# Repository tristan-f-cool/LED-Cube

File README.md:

# 3×3×3 Blue LED Cube

A 27-LED cube built around a custom ATmega328P controller PCB, programmed using the Arduino Uno platform. This project brings together the PCB design, Arduino firmware, and a 3D-printable base platform stand.

The animations are written as individual C++ functions, with reusable helpers for LEDs, layers, columns, and faces.

**[Watch the cube on YouTube](https://youtu.be/wXxeV7et9vc?si=_cEj829iDm0wTGiT)**

## Project at a glance

| Feature | Details |
| --- | --- |
| Display | 3 layers × 9 columns: 27 blue LEDs |
| Controller | ATmega328P on a custom PCB |
| Firmware | Arduino sketch with 16 effect functions |
| Playback | Sequential, random, or development mode |
| Hardware design | EAGLE schematic, board layout, and exported parts list |
| Mechanical design | STL files for the base and a separate LED grid |

## Hardware

The controller uses nine column outputs and three transistor-switched layer outputs. The firmware uses Arduino pin names, so the same mapping is easy to follow when working with an Uno-compatible ATmega328P setup.

| Connection | Arduino pins | Circuit |
| --- | --- | --- |
| Columns 1–9 | D2–D10, respectively | 220 Ω series resistors |
| Layers 1–3 | A0–A2, respectively | 2N3904 NPN layer drivers |
| Serial diagnostics | Serial at 9600 baud | Effect and playback-mode messages |

The schematic includes a 16 MHz crystal, reset circuit, 7805 regulator, serial programming header, and ICSP header. See the design files and parts list for the full circuit.

<details>
<summary>Schematic</summary>

</details>

| PCB layout | PCB 3D view |
| --- | --- |
|  |  |

- [EAGLE schematic](PCB/LEDCube-3x3x3/LEDCube-3x3x3.sch)
- [EAGLE board](PCB/LEDCube-3x3x3/LEDCube-3x3x3.brd)
- [Exported parts list](PCB/LEDCube-3x3x3/LEDCube-3x3x3-PCBA_BOM.txt)
- [Archived PCB design package](PCB/LEDCube-3x3x3/LEDCube-3x3x3_2026-02-08.zip)

## Firmware

The complete sketch is in [`code/LEDCube-3x3x3/LEDCube-3x3x3.ino`](code/LEDCube-3x3x3/LEDCube-3x3x3.ino). It uses Arduino core functions and has no external library includes.

### Program flow

```mermaid
flowchart TD
    A[Power on or reset] --> B["setup(): start Serial, seed random generator, configure pins"]
    B --> C["loop(): read playback setting"]
    C --> D{Mode}
    D -->|DEV| E[Select effect 0]
    D -->|SEQUENCE| F[Advance effect index; wrap after 15]
    D -->|RANDOM| G[Choose effect index from 0 to 15]
    E --> H["LEDCube(): log index and dispatch effect"]
    F --> H
    G --> H
    H --> I["Effect0() through Effect15()"]
    I --> J[LED, layer, column, and face helpers]
    J --> K["digitalWrite() and delay()"]
    K --> L[Clear LEDs and pause 500 ms]
    L --> C
```

Effects directly set the layer and column outputs and use blocking delays for timing. There is no separate background display-refresh task in this sketch.

### Playback modes

Change the setting near the top of the sketch before uploading:

```cpp
mode setting = SEQUENCE;
```

| Mode | Behavior |
| --- | --- |
| `DEV` | Repeats `Effect0()` for development and testing |
| `SEQUENCE` | Advances through effect indices, wrapping from 15 to 0 |
| `RANDOM` | Selects an effect index with `random(16)` |

In the current sketch, `effect_index` starts at 0 and is incremented before dispatch in `SEQUENCE` mode, so the first effect after reset is `Effect1()`.

### Included effects

| Function | Animation |
| --- | --- |
| `Effect0()` | Full-cube flashing with decreasing delay |
| `Effect1()` | Random LED flashes |
| `Effect2()` | Alternating corners and center |
| `Effect3()` | Full-column spirals |
| `Effect4()` | Random columns moving up and down |
| `Effect5()` | Layer spirals, inward and outward |
| `Effect6()` | Traveling faces along the three axes |
| `Effect7()` | Alternating X and cross patterns |
| `Effect8()` | Corners and diamonds |
| `Effect9()` | Spinning faces through the center |
| `Effect10()` | Rotating perimeter faces |
| `Effect11()` | Perimeter column chase |
| `Effect12()` | Perimeter wave |
| `Effect13()` | Figure-eight paths |
| `Effect14()` | Zigzag paths |
| `Effect15()` | Three-dimensional X paths |

### Writing an effect

The helper API uses **layer numbers 1–3** and **column numbers 1–9**. For example:

```cpp
void MyEffect()
{
  LED_ALL_OFF();
  LED_ON(1, 5);       // Center LED of the bottom layer
  delay(200);
  LED_ALL_OFF();
  LAYER_SQUARE(3);   // Perimeter of the top layer
  delay(200);
  LED_ALL_OFF();
}
```

To add an effect, give it a case in `LEDCube()` and update both the sequential wrap limit and random-selection range. Outputs remain set until another helper changes them; clear the previous pattern when needed.

Column numbering follows the sketch's wiring diagram, repeated on each layer:

```text
1   4   7
2   5   8
3   6   9
```

Layer 1 is the bottom, layer 2 is the middle, and layer 3 is the top.

### Current source notes

The checked-in firmware has a few items to review before extending it:

- `LED_ALL_ON()` and `LED_ALL_OFF()` iterate through layer 4 and column 10, beyond the arrays. Their valid limits are 3 layers and 9 columns.
- `LED_RANDOM_ON()` and `LED_RANDOM_OFF()` can generate zero, although the helper API is one-based. `Effect4()` also uses `random(10)` for a column and can select zero. Valid selections use `random(1, 4)` for layers and `random(1, 10)` for columns.
- The dispatch case for effect 10 has no `break`, so selecting effect 10 also runs effect 11.
- The firmware comment describes 2.2 kΩ transistor base resistors, while the schematic and exported parts list specify 22 kΩ. Confirm the fitted values against your board revision.

These notes describe the source as supplied; they are not firmware changes.

## Loading the sketch

1. Open `code/LEDCube-3x3x3/LEDCube-3x3x3.ino` in the Arduino IDE.
2. Select the Arduino Uno target for an ATmega328P configured with the Uno bootloader and 16 MHz clock.
3. Choose the desired playback mode in the sketch.
4. Upload using your board's programming connection. A chip without a bootloader needs an ISP programmer to provision it or program the firmware directly.
5. Open Serial Monitor at **9600 baud** to see the mode and effect index.

## Printed base and CAD

The printed base supports the controller PCB and gives the cube a finished platform.

- [Base platform STL](CAD/base.stl)
- [LED grid STL](CAD/ledgrid4x4.stl) — a separate 4×4 grid model included in the repository; the electronic cube documented here is 3×3×3.

<details>
<summary>LED grid render</summary>

</details>

<!-- Add your preferred material, layer height, infill, support settings, and mounting hardware here. -->

## Repository guide

```text
.
├── CAD/                         Base and LED grid STL files
├── code/LEDCube-3x3x3/          Arduino firmware
├── PCB/LEDCube-3x3x3/           EAGLE files, parts list, and archive
├── media/                       Photos, design renders, and demo videos
├── .gitattributes               Git LFS tracking rules
└── README.md
```

### Photos and video

Watch the [YouTube demonstration](https://youtu.be/wXxeV7et9vc?si=_cEj829iDm0wTGiT), or download the original clips: [demo](media/demo.mp4), [dark-room demo](media/demo-dark.mp4), and [demo 2](media/demo2.mp4).

### Getting the media and CAD files

The binary assets use Git LFS. With Git LFS installed, clone the repository and retrieve its assets:

```sh
git lfs install
git clone https://github.com/tristan-f-cool/LED-Cube.git
cd LED-Cube
git lfs pull
```

If an image or STL opens as a short text file beginning with `version https://git-lfs.github.com/spec/v1`, it is an LFS pointer; run `git lfs pull` to retrieve the actual asset.

## Author

Designed and built by **Tristan Cool**.

<!-- Add a LICENSE file and a license section when you have chosen terms for the hardware, firmware, and CAD. -->

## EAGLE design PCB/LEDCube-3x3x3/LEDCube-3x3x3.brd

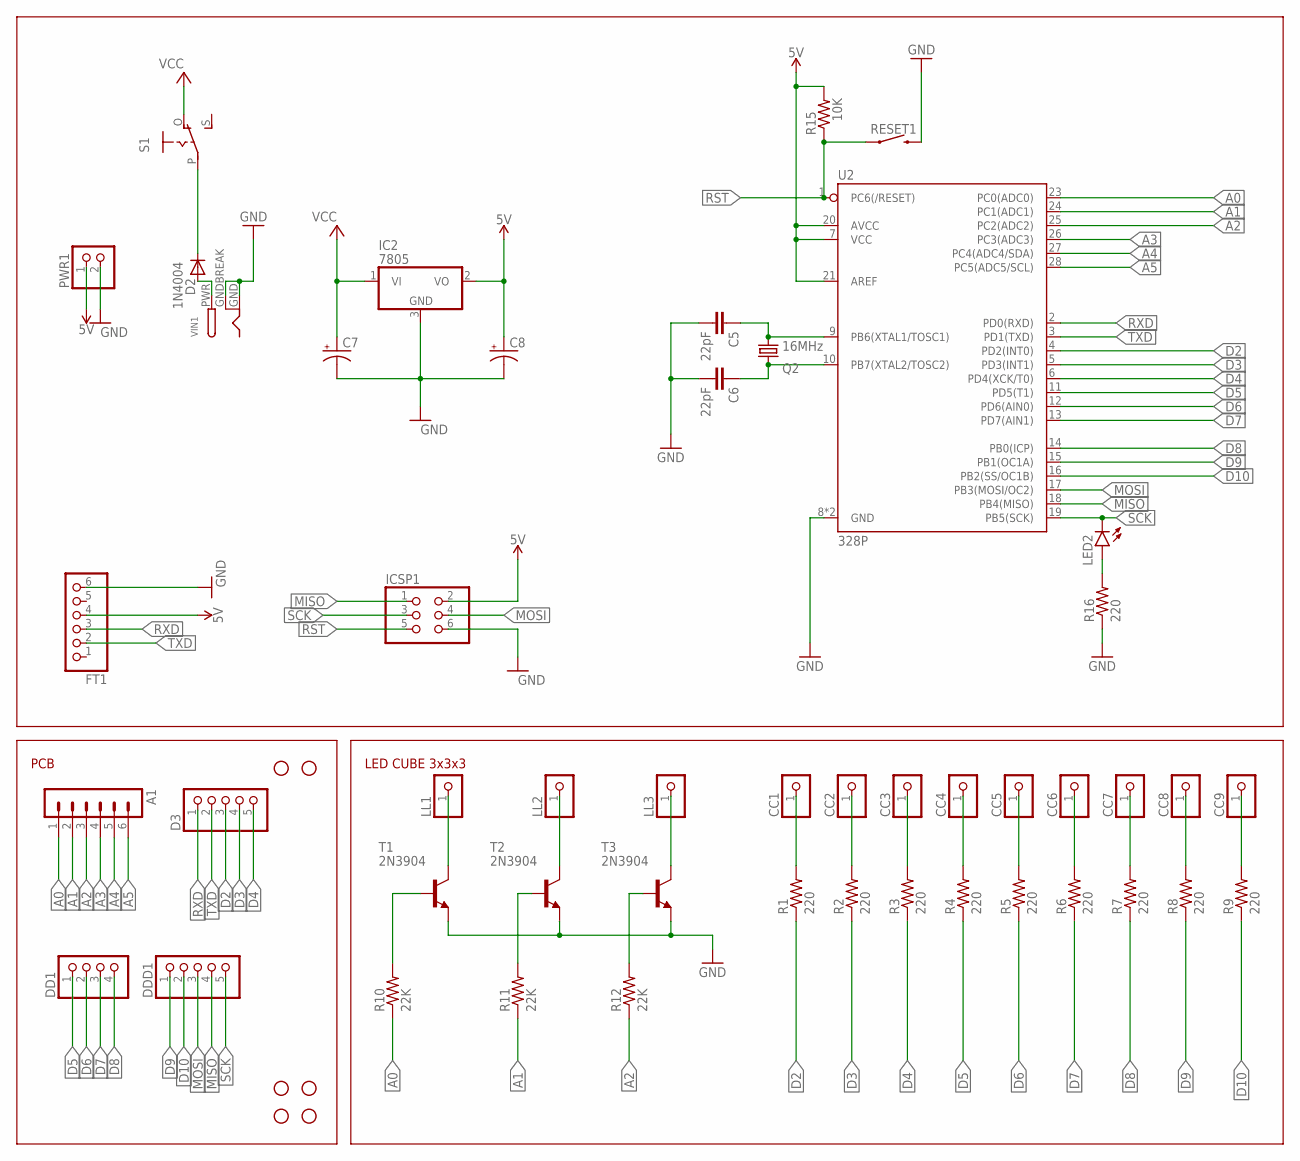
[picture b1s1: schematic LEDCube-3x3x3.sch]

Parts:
A1: MA06-1
C5, C6: 22pF; CAP-PTH-2.54
C7, C8: CPOL-USE1.8-4; E1,8-4
CC1, CC2, CC3, CC4, CC5, CC6, CC7, CC8, CC9: PINHD-1X1; 1X01
D2: 1N4004; DO41-10
D3: PINHD-1X5; 1X05
DD1: PINHD-1X4; 1X04
DDD1: PINHD-1X5; 1X05
FT1: PINHD-1X6; 1X06
H1, H2, H3, H4, H7, H8: STAND-OFFTIGHT; STAND-OFF-TIGHT
IC2: 7805; TO252
ICSP1: PINHD-2X3; 2X03
LED2: LEDCHIP-LED0805; CHIP-LED0805
LL1, LL2, LL3: PINHD-1X1; 1X01
PWR1: PINHD-1X2; 1X02
Q2: 16MHz; HC49/S
R1, R2, R3, R4, R5, R6, R7, R8, R9, R16: 220; R0805
R10, R11, R12: 22K; R0805
R15: 10K; R0805
RESET1: MOMENTARY-SWITCH-SPST-PTH-6.0MM; TACTILE_SWITCH_PTH_6.0MM
S1: EG1218S; EG1218
T1, T2, T3: 2N3904; TO92
U2: 328P; DIP28
VIN1: DCBARRELPTH; DCJACK_2MM_PTH

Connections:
5V: C8.+, FT1.4, IC2.2 (VO), ICSP1.2, PWR1.1, R15.2, U2.7 (VCC), U2.20 (AVCC), U2.21 (AREF)
A0: A1.1, R10.1, U2.23 (PC0(ADC0))
A1: A1.2, R11.1, U2.24 (PC1(ADC1))
A2: A1.3, R12.1, U2.25 (PC2(ADC2))
A3: A1.4, U2.26 (PC3(ADC3))
A4: A1.5, U2.27 (PC4(ADC4/SDA))
A5: A1.6, U2.28 (PC5(ADC5/SCL))
C3: CC3.1, R3.2
D2: D3.3, R1.1, U2.4 (PD2(INT0))
D3: D3.4, R2.1, U2.5 (PD3(INT1))
D4: D3.5, R3.1, U2.6 (PD4(XCK/T0))
D5: DD1.1, R4.1, U2.11 (PD5(T1))
D6: DD1.2, R5.1, U2.12 (PD6(AIN0))
D7: DD1.3, R6.1, U2.13 (PD7(AIN1))
D8: DD1.4, R7.1, U2.14 (PB0(ICP))
D9: DDD1.1, R8.1, U2.15 (PB1(OC1A))
D10: DDD1.2, R9.1, U2.16 (PB2(SS/OC1B))
GND: C5.2, C6.2, C7.-, C8.-, FT1.6, IC2.3 (GND), ICSP1.6, PWR1.2, R16.1, RESET1.3 (2), T1.3 (E), T2.3 (E), T3.3 (E), U2.8 (GND), U2.22 (GND), VIN1.GND, VIN1.GNDBREAK
MISO: DDD1.4, ICSP1.1, U2.18 (PB4(MISO))
MOSI: DDD1.3, ICSP1.4, U2.17 (PB3(MOSI/OC2))
unnamed: R10.2, T1.2 (B)
unnamed: R11.2, T2.2 (B)
unnamed: R12.2, T3.2 (B)
unnamed: LL1.1, T1.1 (C)
unnamed: D2.C, S1.P
unnamed: LL2.1, T2.1 (C)
unnamed: LL3.1, T3.1 (C)
unnamed: CC1.1, R1.2
unnamed: CC2.1, R2.2
unnamed: CC4.1, R4.2
unnamed: CC5.1, R5.2
unnamed: CC6.1, R6.2
unnamed: CC7.1, R7.2
unnamed: CC8.1, R8.2
unnamed: CC9.1, R9.2
unnamed: C5.1, Q2.1, U2.9 (PB6(XTAL1/TOSC1))
unnamed: C6.1, Q2.2, U2.10 (PB7(XTAL2/TOSC2))
unnamed: LED2.A, R16.2
unnamed: D2.A, VIN1.PWR
RST: ICSP1.5, R15.1, RESET1.1, U2.1 (PC6(/RESET))
RXD: D3.1, FT1.3, U2.2 (PD0(RXD))
SCK: DDD1.5, ICSP1.3, LED2.C, U2.19 (PB5(SCK))
TXD: D3.2, FT1.2, U2.3 (PD1(TXD))
VCC: C7.+, IC2.1 (VI), S1.O

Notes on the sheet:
PCB
LED CUBE 3x3x3

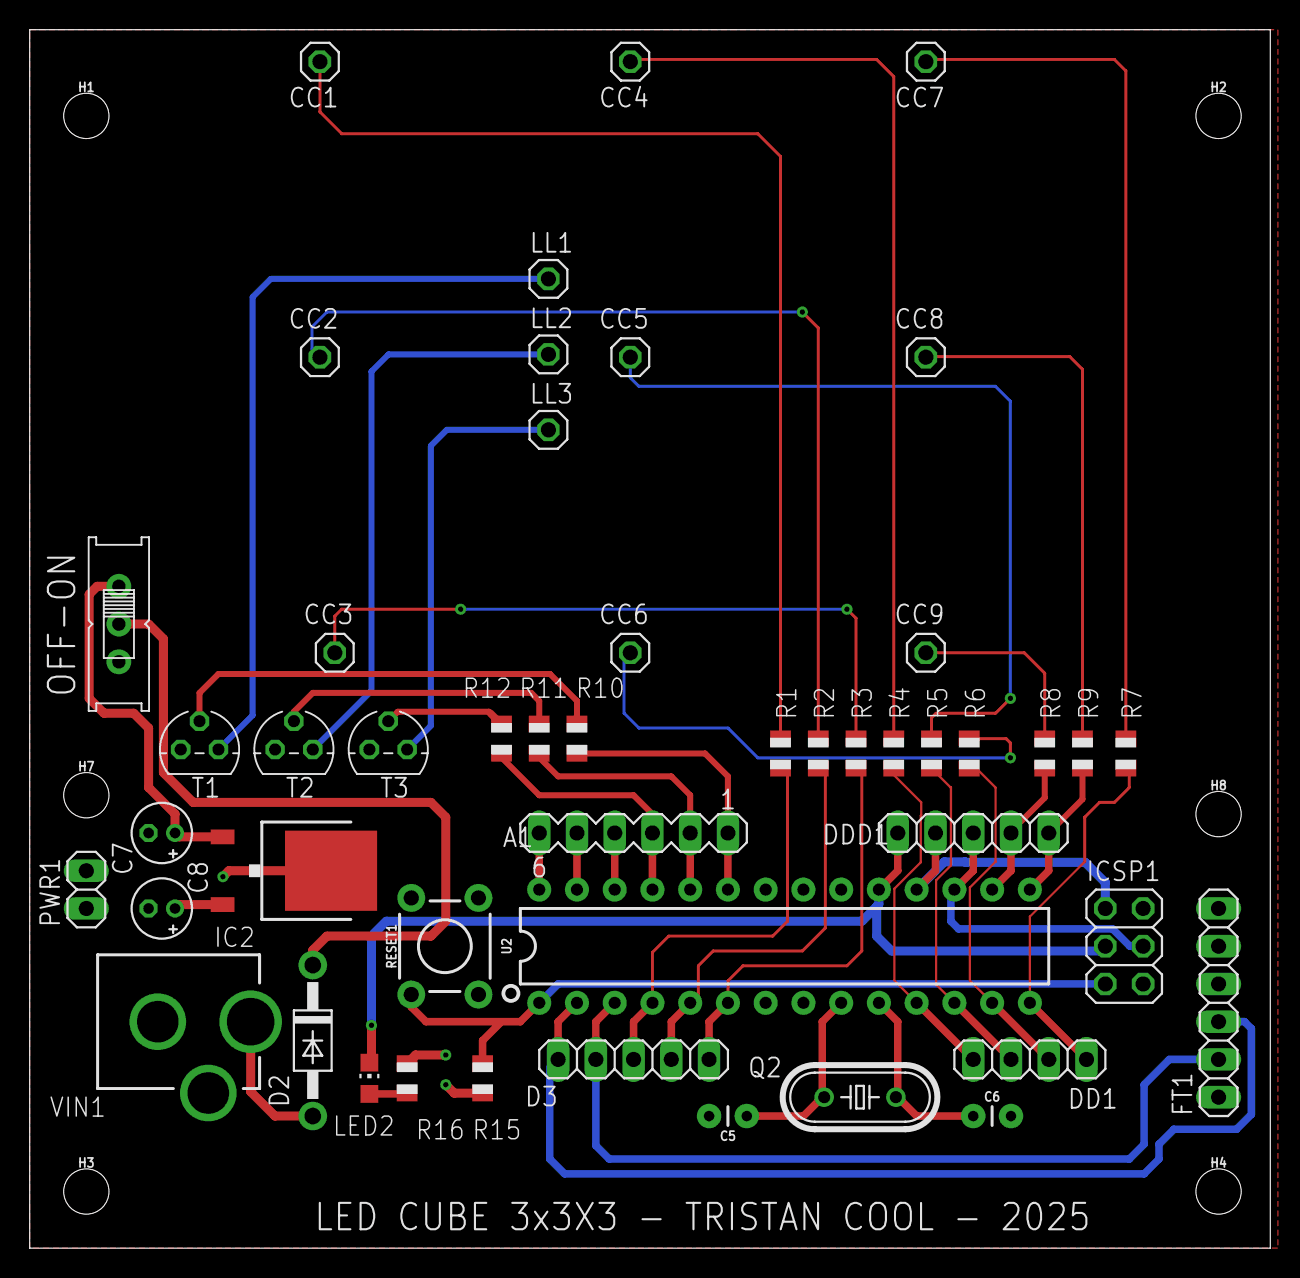
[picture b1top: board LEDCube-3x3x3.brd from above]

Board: 2 copper layers, 83.5 x 82.0 mm, 54 parts (0 on the bottom side), 44 nets.

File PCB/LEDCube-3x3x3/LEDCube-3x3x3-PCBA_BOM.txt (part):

Partlist exported from T:/Eagle_/LEDCube-3x3x3/LEDCube-3x3x3.sch at 5/19/2026 6:13 PM

Part   Value          Device                          Package                  Description                          MF MPN OC_FARNELL OC_NEWARK POPULARITY PROD_ID     SF_SKU    VALUE
A1                    MA06-1                          MA06-1                   PIN HEADER                                  unknown    unknown   28                                    
C5     22pF           22PF-PTH-2.54MM-200V-5%         CAP-PTH-2.54             22pF ceramic capacitors                                                     CAP-09128             22pF 
C6     22pF           22PF-PTH-2.54MM-200V-5%         CAP-PTH-2.54             22pF ceramic capacitors                                                     CAP-09128             22pF 
C7                    CPOL-USE1.8-4                   E1,8-4                   POLARIZED CAPACITOR, American symbol                                                                   
C8                    CPOL-USE1.8-4                   E1,8-4                   POLARIZED CAPACITOR, American symbol                                                                   
CC1                   PINHD-1X1                       1X01                     PIN HEADER                                                       64                                    
CC2                   PINHD-1X1                       1X01                     PIN HEADER                                                       64                                    
CC3                   PINHD-1X1                       1X01                     PIN HEADER                                                       64                                    
CC4                   PINHD-1X1                       1X01                     PIN HEADER                                                       64                                    
CC5                   PINHD-1X1                       1X01                     PIN HEADER                                                       64                                    
CC6                   PINHD-1X1                       1X01                     PIN HEADER                                                       64                                    
CC7                   PINHD-1X1                       1X01                     PIN HEADER                                                       64                                    
CC8                   PINHD-1X1                       1X01                     PIN HEADER                                                       64                                    
CC9                   PINHD-1X1                       1X01                     PIN HEADER                                                       64                                    
D2     1N4004         1N4004                          DO41-10                  DIODE                                                                                                  
D3                    PINHD-1X5                       1X05                     PIN HEADER                                                       69                                    
DD1                   PINHD-1X4                       1X04                     PIN HEADER                                                       91                                    
DDD1                  PINHD-1X5                       1X05                     PIN HEADER                                                       69                                    
FT1                   PINHD-1X6                       1X06                     PIN HEADER                                                       79                                    
H1     STAND-OFFTIGHT STAND-OFFTIGHT                  STAND-OFF-TIGHT          Stand Off                                                                                              
H2     STAND-OFFTIGHT STAND-OFFTIGHT                  STAND-OFF-TIGHT          Stand Off                                                                                              
H3     STAND-OFFTIGHT STAND-OFFTIGHT                  STAND-OFF-TIGHT          Stand Off                                                                                              
H4     STAND-OFFTIGHT STAND-OFFTIGHT                  STAND-OFF-TIGHT          Stand Off                                                                                              
H7     STAND-OFFTIGHT STAND-OFFTIGHT                  STAND-OFF-TIGHT          Stand Off                                                                                              
H8     STAND-OFFTIGHT STAND-OFFTIGHT                  STAND-OFF-TIGHT          Stand Off                                                                                              
IC2    7805           7806DT                          TO252                    Positive VOLTAGE REGULATOR                                       18                                    
ICSP1                 PINHD-2X3                       2X03                     PIN HEADER                                                       62                                    
LED2                  LEDCHIP-LED0805                 CHIP-LED0805             LED                                                              68                                    
LL1                   PINHD-1X1                       1X01                     PIN HEADER                                                       64                                    
LL2                   PINHD-1X1                       1X01                     PIN HEADER                                                       64                                    
LL3                   PINHD-1X1                       1X01                     PIN HEADER                                                       64                                    
PWR1                  PINHD-1X2                       1X02                     PIN HEADER                                                       98                                    
Q2     16MHz          CRYSTALHC49S                    HC49/S                   CRYSTAL                                     1667008    unknown   49                                    
R1     220            R-US_R0805                      R0805                    RESISTOR, American symbol                                                                              
R2     220            R-US_R0805                      R0805                    RESISTOR, American symbol                                                                              
R3     220            R-US_R0805                      R0805                    RESISTOR, American symbol                                                                              
R4     220            R-US_R0805                      R0805                    RESISTOR, American symbol                                                                              
R5     220            R-US_R0805                      R0805                    RESISTOR, American symbol                                                                              
R6     220            R-US_R0805                      R0805                    RESISTOR, American symbol                                                                              
R7     220            R-US_R0805                      R0805                    RESISTOR, American symbol                                                                              
R8     220            R-US_R0805                      R0805                    RESISTOR, American symbol                                                                              
R9     220            R-US_R0805                      R0805                    RESISTOR, American symbol                                                                              
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
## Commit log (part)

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2026-05-19 Eagle PCB schematic, layout and gerber manufacturing files
2026-05-19 Arduino (Atmega 328P) application firmware

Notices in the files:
parts and their libraries:
SparkFun-Hardware: Licensing: Creative Commons ShareAlike 4.0 International - https://creativecommons.org/licenses/by-sa/4.0
